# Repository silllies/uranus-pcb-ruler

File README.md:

# uranus-pcb-ruler

The all new patent pending Uranus PCB Ruler is a Ruler on a PCB made all for PCBs!

**Features!!:**

- Centimeter and decimal inch scale up to 20cm
- Ultrafine scale for the first 3cm/inch
- NFC tag and antenna to quickly send your NFC capable device to your favorite website
- Alternating copper pours to easily discern inches/centimeters
- Simple math table for quick calculations
- Simple unit conversion formula
- Symbol tables for easy searching, grouped by vibe
- A motivational quote!
- Trace width scale
- Pad pitch scale
- A whole bunch of common footprints, including
	- 0201 to 2920 passive sizes
	- DSBGA (0.4 and 0.5mm)
	- BGA-49 (0.4, 0.5, and 0.65mm)
	- BGA-96
	- eMMC BGA-153
	- TSSOP-16
	- QFN-32 (0.4, 0.5, and 0.65mm)
	- DFN-16 (3x4 and 5x5mm)
	- L/TQFP-32 (5x5 and 7x7mm)
	- SOT-23
	- SC-70
	- SOIC-16W
	- SOIC-8
	- SMA-C
	- MicroMELF-MELF
	- SOT-223
- Car. Vroom vroom
- Silkscreen text height/width in mils

**Why did I make this?**  
I have a very bad sense of scale, and I really want the Fabricate dev board (I was working on a very complex project that wouldn't be finished in time)

**Why Uranus?**  
No, it's not because I think it's funny. Uranus' pronunciation starts with YOOR. I chose Uranus because ~~it is a cool planet~~ Uranus is the god of the sky and heavens, and this ruler is PEAK, so much so, in fact, that it reaches the sky and heavens.

**Why is there an NFC tag?**  
This ruler has a multitude of common footprints so that you can quickly see what they look like and their size. The NFC tag follows that by giving you a way to quickly get to your favorite website that may, or may not, be related to PCBs.

**Why aren't there footprints by the antenna, and why are the measure lines squashed?**  
The footprints and measure lines are created from revealed copper (with HASL covering). Antennas are very sensitive devices, and copper can mess with it. Some of those ways include eddy currents, which reduce the effective range of the antenna; inductance drop, which changes the resonant frequency of the antenna; and Q-factor degradation, which happens from the copper stealing energy from the system. Because of this, it is recommended to keep copper 5mm away from the antenna. I compromised with 4mm, as 5mm started taking up too much space.

**Why is the antenna so loopy?**  
The resonant frequency of an antenna is calculated with the following formula

$$f_{0}=\frac{1}{2\pi\sqrt{L\cdot C}}$$

For an NFC antenna, the frequency should be 13.56 MHz. The wavelength of that frequency is about 22 meters. My antenna does not approach the length of a half wavelength, so I must tune (primarily) for inductance. Most NFC tags have a built in tuning capacitor that gives you a baseline capacitance, mine is 28.5 pF. From that, you can calculate your desired inductance and then build an antenna from there. The antenna ends up being so loopy because every copper trace has a magnetic field it generates, and having a whole bunch of parallel traces in the same direction multiplies the size of it. Inductance is just the measure of how well a conductor opposes changes in current with aid from a magnetic field. When the current changes, the magnetic field also changes, which induces a voltage that opposes the change.

**Why is the antenna on 2 layers?**  
This is another space saving optimization I made. When you have a typical one layer antenna, it keeps spiraling into its center. As it gets closer, it gets less and less effective at increasing the inductance. I would need to use a larger square, which would eat up more space. I realized splitting the antenna onto two layers would help by pushing several turns onto a fresh, already unused space, and also help increase the inductance per turn more by also increasing mutual coupling. Care must be taken, though, as the current must flow in the same direction as the top layer. Having current flow in opposite directions will make have the mutual coupling that was aiding your antenna fight against it. An unforeseen benefit of having a two layered antenna is that the ends of the antenna will end up being right next to one another, which means one trace does not have to cross all over your specially organized copper.

**If you kept copper away from the antenna by 4mm, why is the NFC tag in the dead center?**  
NFC doesn't work like standard wireless communication, like bluetooth or wifi. Those systems emit light at radio frequencies, and the power of those signals drop according to the inverse square law ($\frac{1}{r^{2}}$). NFC works instead by generating a local magnetic field, and the power of that signal drops to the inverse of the distance to the sixth power ($\frac{1}{r^{6}}$). Because of this, travelling just a bit away greatly diminishes the power, and the NFC tag is powered entirely by energy harvesting.

**Does your design pass DRC?**  
Uhhhhh, depends on your definition of "pass". DRC is very angry at me, but everything it is angry at me for is completely intentional, and thus, ignored.

PCB Designs:

Schematic:

OnShape Link: https://cad.onshape.com/documents/8c18ba316aef32837132ded3/w/c63f49af48b50d1a20b8cf42/e/5f7f85fcc015b1d66f8c32cf?renderMode=0&uiState=6ae67d3631cfde5853118ce8

BOM:

| Reference | MPN | Manufacturer | Price | Count | Description | Link
| --------- | --- | ------------ | ----- | ----- | ----------- | ----
| C1 | C0402C152F5GECAUTO | KEMET | 0.60 | 1 | 1.5nF C0G ±1% 50V 0402 Ceramic Capacitors RoHS | https://www.lcsc.com/product-detail/C3875817.html
| U1 | ST25DV04KC-IE8S3 | ST | 0.90 | 1 | NFC RFID Tag 4 Kbit | https://www.lcsc.com/product-detail/C5221752.html
| | | | 23.61 | | LCSC Fees |
| | | | 8.20 | 5 (included) | JLCPCB Board |
| | | | 14.4 | | JLCPCB Fees |
| | | Total | 47.71 | | | |

I cannot properly estimate the final price, as I will be linking my LCSC order to my JLCPCB order, which can only happen after the JLCPCB order is placed. It may be around $12-16 in savings

AI Disclosure:

I used AI to help with estimating the inductance and capacitance of the antenna

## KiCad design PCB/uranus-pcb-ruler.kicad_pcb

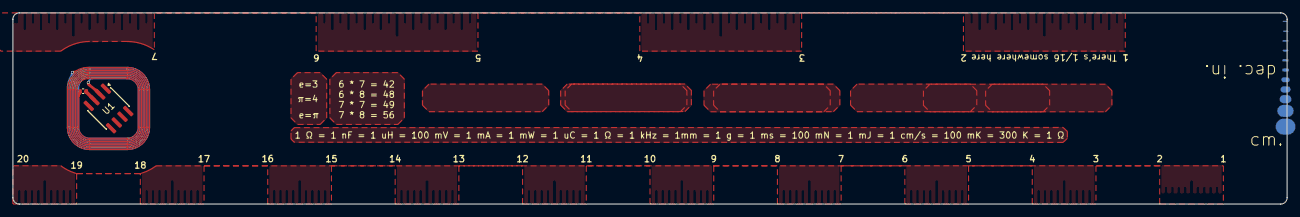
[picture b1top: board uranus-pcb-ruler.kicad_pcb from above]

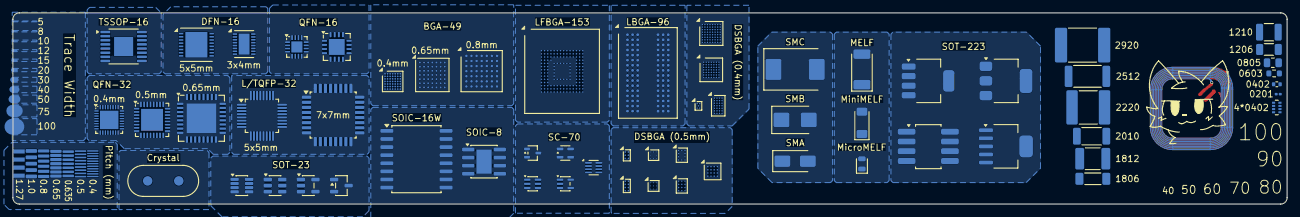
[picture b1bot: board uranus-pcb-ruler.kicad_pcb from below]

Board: 2 copper layers, 200.0 x 30.0 mm, 43 parts (41 on the bottom side), 2 nets.

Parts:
0.4mm: UCBGA-49_3x3mm_Layout7x7_P0.4mm
0.4mm#2: QFN-32-1EP_4x4mm_P0.4mm_EP2.9x2.9mm
0.8mm: Analog_BGA-49_6.25x6.25mm_Layout7x7_P0.8mm
0.65mm: QFN-32-1EP_7x7mm_P0.65mm_EP4.65x4.65mm
3x4mm: DFN-16-1EP_3x4mm_P0.45mm_EP1.7x3.3mm
4*0402: R_Array_Concave_4x0402
7x7mm: LQFP-32_7x7mm_P0.8mm
0201: R_0201_0603Metric
0402: R_0402_1005Metric
0603: R_0603_1608Metric
0805: R_0805_2012Metric
1206: R_1206_3216Metric
1210: R_1210_3225Metric
1806: L_1806_4516Metric
1812: C_1812_4532Metric
2010: R_2010_5025Metric
2220: C_2220_5750Metric
2512: R_2512_6332Metric
2920: Fuse_2920_7451Metric
BGA-49: VFBGA-49_5.0x5.0mm_Layout7x7_P0.65mm
C2: 0F; C_0402_1005Metric
Crystal: Crystal_HC49-U_Vertical
DFN-16: DFN-16-1EP_5x5mm_P0.5mm_EP3.46x4mm
DSBGA (0.4mm): Texas_DSBGA-64_3.415x3.535mm_Layout8x8_P0.4mm
DSBGA (0.5mm): Texas_DSBGA-8_0.9x1.9mm_Layout2x4_P0.5mm
L/TQFP-32: LQFP-32_5x5mm_P0.5mm
LBGA-96: Micron_FBGA-96_9x14mm_Layout9x16_P0.8mm
LFBGA-153: LFBGA-153_11.5x13mm_Layout14x14_P0.5mm
MELF: D_MELF
MicroMELF: D_MicroMELF
MiniMELF: D_MiniMELF
QFN-16: QFN-16-1EP_3x3mm_P0.5mm_EP1.75x1.75mm
QFN-32: QFN-32-1EP_5x5mm_P0.5mm_EP3.45x3.45mm
SC-70: SOT-323_SC-70
SMA: D_SMA
SMB: D_SMB
SMC: D_SMC
SOIC-8: SOIC-8-1EP_3.9x4.9mm_P1.27mm_EP2.41x3.81mm
SOIC-16W: SOIC-16W_7.5x10.3mm_P1.27mm
SOT-23: SOT-23-6
SOT-223: SOT-223
TSSOP-16: TSSOP-16-1EP_4.4x5mm_P0.65mm_EP3x3mm
U1: ST25DV04KC-IE8S3; SOIC-8_3.9x4.9mm_P1.27mm

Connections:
unnamed: C2.1, U1.2 (AC0)
unnamed: C2.2, U1.3 (AC1)
